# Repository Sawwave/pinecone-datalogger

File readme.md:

Arm based Datalogger running the Atmel SAM D20 MCU.

The Pinecone logger is a specialized, yet inexpensive data logger intended for sensing environmental variables. The ease of use and low cost of these datalogger systems make them ideal for mass deployment over a large area, allowing measurement of spatially-distributed data, rather than just a time-series of one point from a single logger.

The logger supports the following sensors natively:
	DHT-22 Temperature and Humidity sensor
	1 potentiometer implemented as a point dendrometer with 14 bits of precision
	multiple ports supporting sensors implementing the SDI-12 interface, which includes most Decagon brand sensors
	1 sap flow sensor implemented with a heating element and 4 thermocouples.

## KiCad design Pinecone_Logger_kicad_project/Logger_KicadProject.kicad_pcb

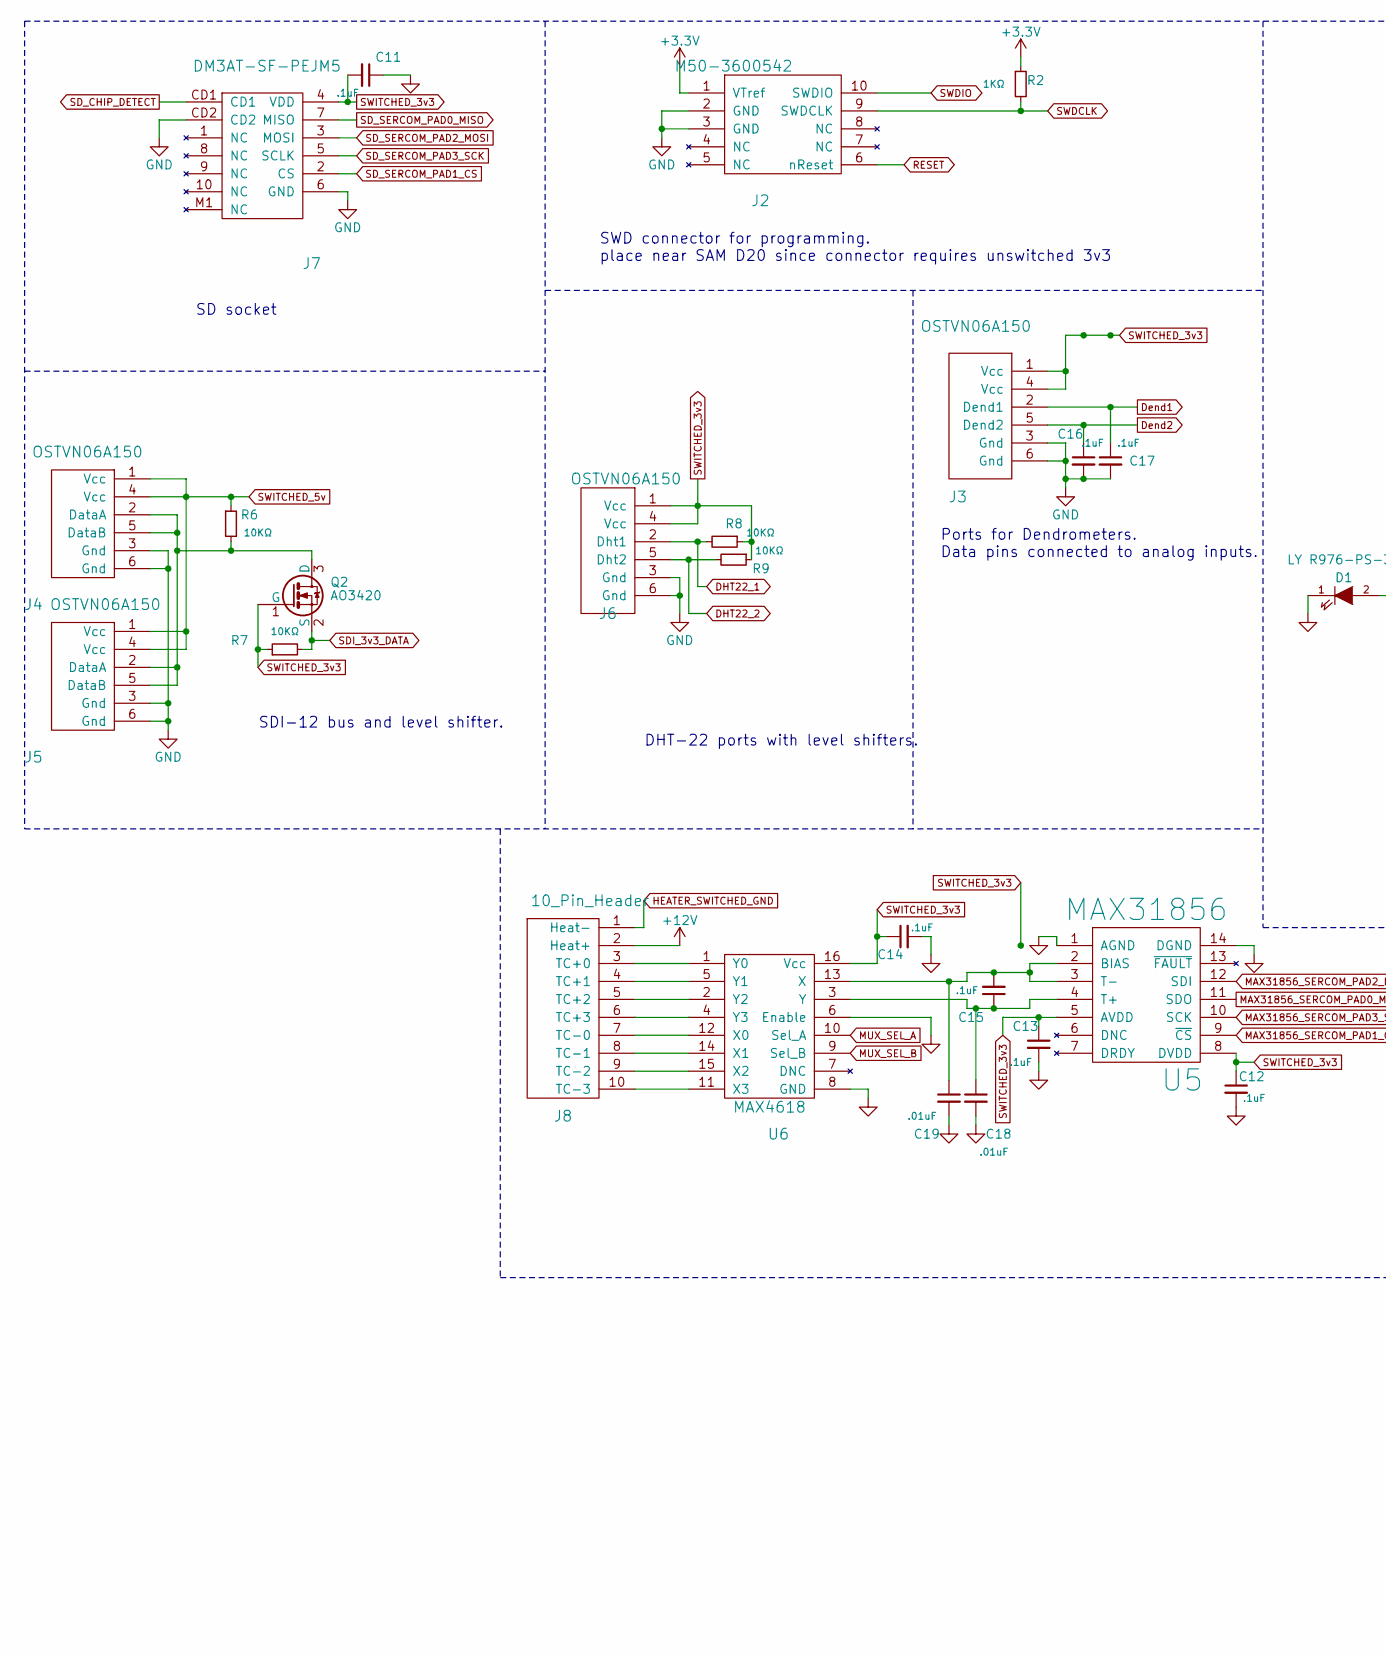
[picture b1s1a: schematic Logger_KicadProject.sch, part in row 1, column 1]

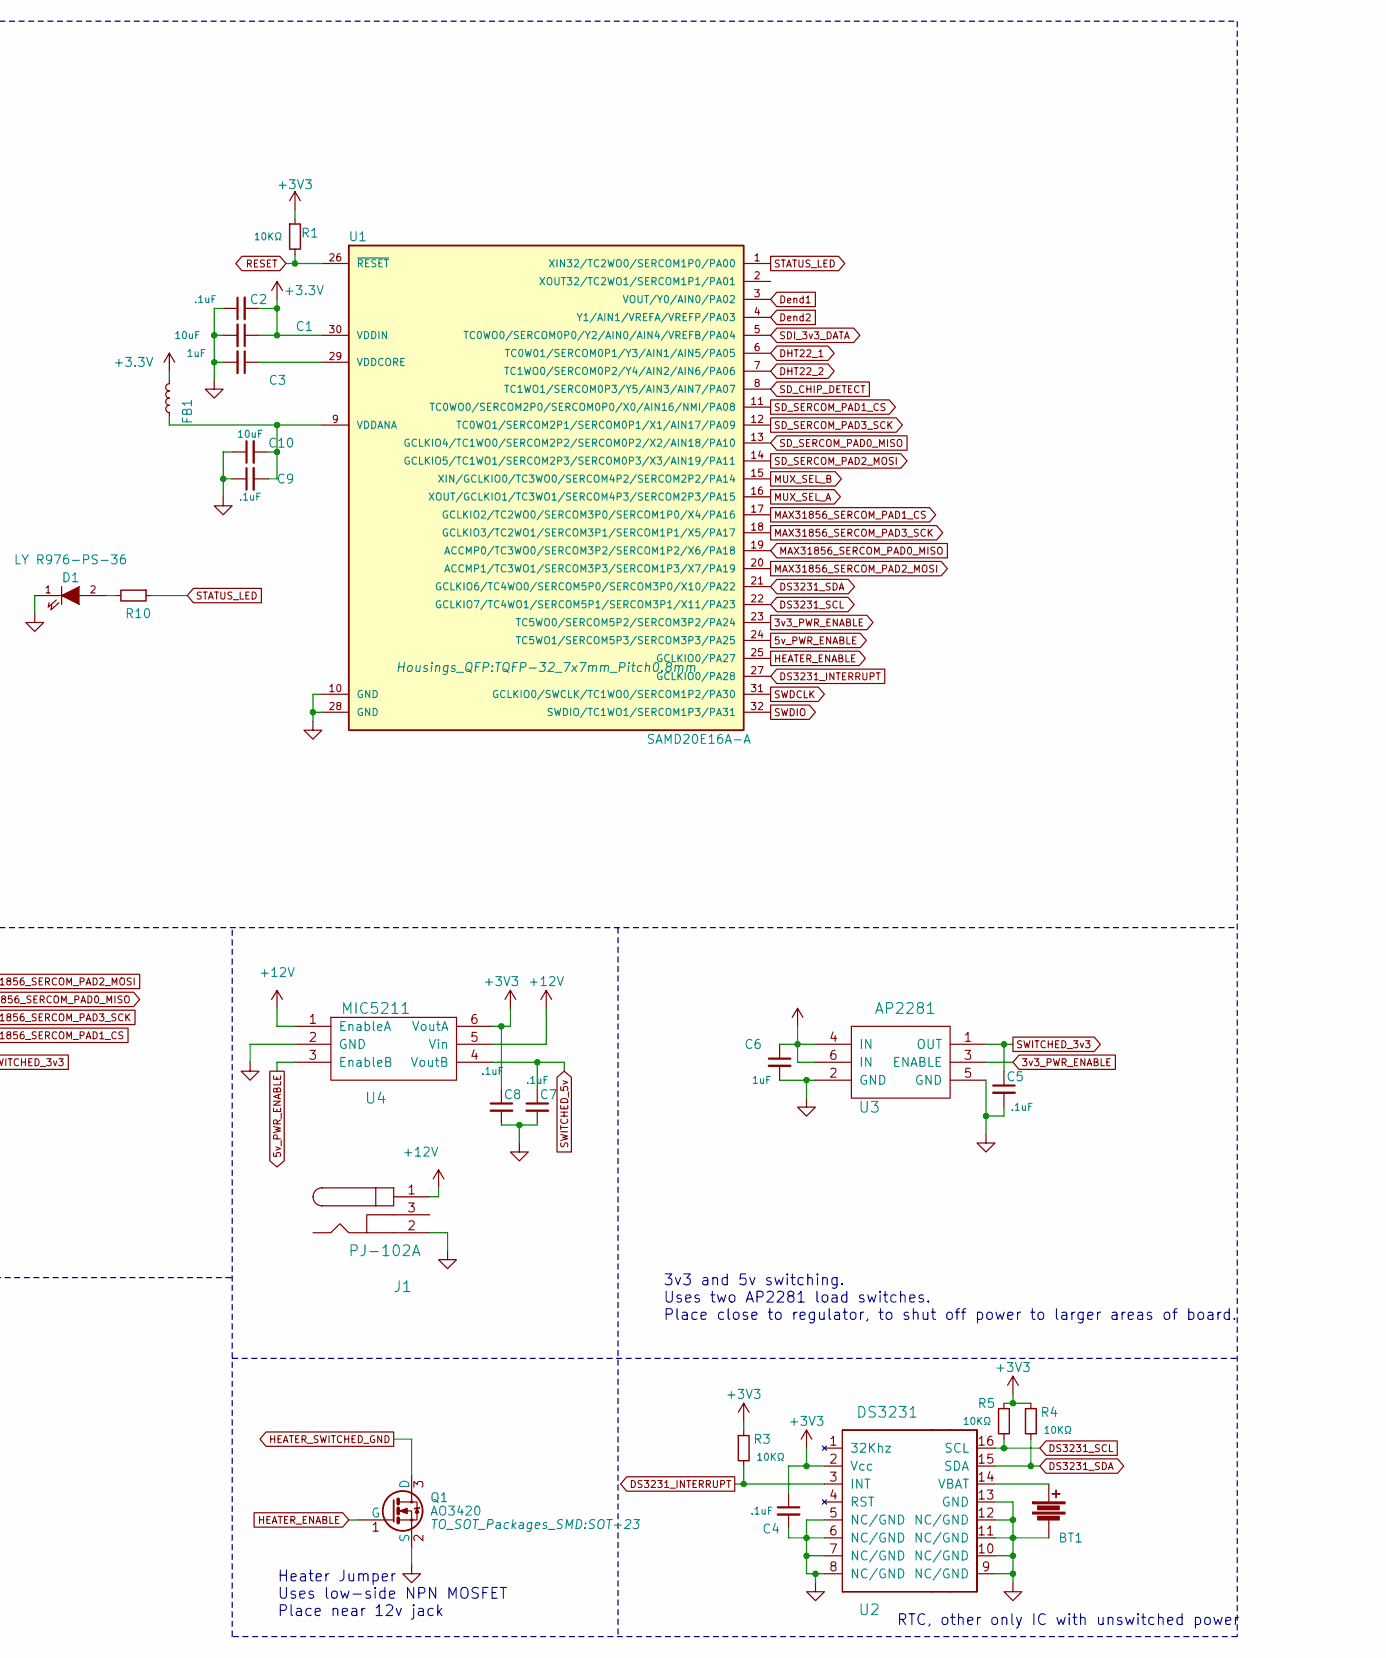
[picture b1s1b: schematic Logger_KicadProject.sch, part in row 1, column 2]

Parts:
BT1: Battery; S8201R_Batt_Holder; Part Id S8201-46R
C1, C10: GRM219R61A106KE44D; C_0805
C2, C4, C5, C7, C8, C9, C11, C12, C13, C14, C15, C16, C17: C0805C104K5RACTU; C_0805
C3, C6: GRM21BR71C105KA01L; C_0805
C18, C19: C0805C103K5RACTU; C_0805
D1: LY R976-PS-36; LED_0805
FB1: Z0805C221APMST; R_0805
J1: PJ-102A
J2: M50-3600542; 10_Pin_Cortex_SMD
J3, J4, J5, J6: OSTVN06A150; OSTVN06A150_6_Pin_Terminal
J7: DM3AT-SF-PEJM5; Hirose_DM3AT
J8: 10_Pin_Header; OSTVN10A150_10_pin_term
Q1, Q2: AO3420; SOT-23
R1, R3, R4, R5, R6, R7, R8, R9: RC0805JR-0710KL; R_0805
R2: RC0805JR-071KL; R_0805
R10: RC0805JR-0768RL; R_0805
U1: SAMD20E16A-A; TQFP-32_7x7mm_Pitch0.8mm
U2: DS3231; SOIC-16W_7.5x10.3mm_Pitch1.27mm
U3: AP2281; SOT-23-6
U4: MIC5211; SOT-23-6
U5: MAX31856; TSSOP-14
U6: MAX4618; SO-16-N

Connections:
3v3_PWR_ENABLE: U1.23 (TC5WO0/SERCOM5P2/SERCOM3P2/PA24), U3.3 (ENABLE)
5v_PWR_ENABLE: U1.24 (TC5WO1/SERCOM5P3/SERCOM3P3/PA25), U4.3 (EnableB)
+12V: J1.1, J8.2 (Heat+), U4.1 (EnableA), U4.5 (Vin)
DHT22_1: J6.2 (Dht1), R8.2, U1.6 (TC0W01/SERCOM0P1/Y3/AIN1/AIN5/PA05)
DHT22_2: J6.5 (Dht2), R9.2, U1.7 (TC1WO0/SERCOM0P2/Y4/AIN2/AIN6/PA06)
DS3231_INTERRUPT: R3.2, U1.27 (GCLKIO0/PA28), U2.3 (INT)
DS3231_SCL: R5.2, U1.22 (GCLKIO7/TC4WO1/SERCOM5P1/SERCOM3P1/X11/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), U2.16 (SCL)
DS3231_SDA: R4.2, U1.21 (GCLKIO6/TC4WO0/SERCOM5P0/SERCOM3P0/X10/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), U2.15 (SDA)
Dend1: C17.1, J3.2 (Dend1), U1.3 (VOUT/Y0/AIN0/PA02)
Dend2: C16.1, J3.5 (Dend2), U1.4 (Y1/AIN1/VREFA/VREFP/PA03)
GND: BT1.2, C1.2, C2.1, C3.2, C4.2, C5.2, C6.2, C7.2, C8.2, C9.1, C10.1, C11.1, C12.2, C13.2, C14.2, C16.2, C17.2, C18.2, C19.2, D1.1 (K), J1.2, J2.2 (GND), J2.3 (GND), J3.3 (Gnd), J3.6 (Gnd), J4.3 (Gnd), J4.6 (Gnd), J5.3 (Gnd), J5.6 (Gnd), J6.3 (Gnd), J6.6 (Gnd), J7.6 (GND), J7.CD2, Q1.2 (S), U1.10 (GND), U1.28 (GND), U2.5 (NC/GND), U2.6 (NC/GND), U2.7 (NC/GND), U2.8 (NC/GND), U2.9 (NC/GND), U2.10 (NC/GND), U2.11 (NC/GND), U2.12 (NC/GND), U2.13 (GND), U3.2 (GND), U3.5 (GND), U4.2 (GND), U5.1 (AGND), U5.14 (DGND), U6.6 (Enable), U6.8 (GND)
HEATER_ENABLE: Q1.1 (G), U1.25 (GCLKIO0/PA27)
HEATER_SWITCHED_GND: J8.1 (Heat-), Q1.3 (D)
MAX31856_SERCOM_PAD0_MISO: U1.19 (ACCMP0/TC3WO0/SERCOM3P2/SERCOM1P2/X6/PA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), U5.11 (SDO)
MAX31856_SERCOM_PAD1_CS: U1.17 (GCLKIO2/TC2WO0/SERCOM3P0/SERCOM1P0/X4/P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), U5.9 (~CS)
MAX31856_SERCOM_PAD2_MOSI: U1.20 (ACCMP1/TC3WO1/SERCOM3P3/SERCOM1P3/X7/PA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), U5.12 (SDI)
MAX31856_SERCOM_PAD3_SCK: U1.18 (GCLKIO3/TC2WO1/SERCOM3P1/SERCOM1P1/X5/P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), U5.10 (SCK)
MUX_SEL_A: U1.16 (XOUT/GCLKIO1/TC3WO1/SERCOM4P3/SERCOM2P3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), U6.10 (Sel_A)
MUX_SEL_B: U1.15 (XIN/GCLKIO0/TC3WO0/SERCOM4P2/SERCOM2P2/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), U6.9 (Sel_B)
unnamed: BT1.1, U2.14 (VBAT)
unnamed: C3.1, U1.29 (VDDCORE)
unnamed: C9.2, C10.2, FB1.1, U1.9 (VDDANA)
unnamed: C15.1, C18.1, U5.4 (T+), U6.3 (Y)
unnamed: C15.2, C19.1, U5.2 (BIAS), U5.3 (T-), U6.13 (X)
unnamed: D1.2 (A), R10.2
unnamed: J4.2 (DataA), J4.5 (DataB), J5.2 (DataA), J5.5 (DataB), Q2.3 (D), R6.2
unnamed: J8.3 (TC+0), U6.1 (Y0)
unnamed: J8.4 (TC+1), U6.5 (Y1)
unnamed: J8.5 (TC+2), U6.2 (Y2)
unnamed: J8.6 (TC+3), U6.4 (Y3)
unnamed: J8.7 (TC-0), U6.12 (X0)
unnamed: J8.8 (TC-1), U6.14 (X1)
unnamed: J8.9 (TC-2), U6.15 (X2)
unnamed: J8.10 (TC-3), U6.11 (X3)
RESET: J2.6 (nReset), R1.2, U1.26 (~RESET~)
SDI_3v3_DATA: Q2.2 (S), R7.2, U1.5 (TC0WO0/SERCOM0P0/Y2/AIN0/AIN4/VREFB/PA04)
SD_CHIP_DETECT: J7.CD1, U1.8 (TC1WO1/SERCOM0P3/Y5/AIN3/AIN7/PA07)
SD_SERCOM_PAD0_MISO: J7.7 (MISO), U1.13 (GCLKIO4/TC1WO0/SERCOM2P2/SERCOM0P2/X2/A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)
SD_SERCOM_PAD1_CS: J7.2 (CS), U1.11 (TC0WO0/SERCOM2P0/SERCOM0P0/X0/AIN16/NMI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)
SD_SERCOM_PAD2_MOSI: J7.3 (MOSI), U1.14 (GCLKIO5/TC1WO1/SERCOM2P3/SERCOM0P3/X3/A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)
SD_SERCOM_PAD3_SCK: J7.5 (SCLK), U1.12 (TC0WO1/SERCOM2P1/SERCOM0P1/X1/AIN17/PA09)
STATUS_LED: R10.1, U1.1 (XIN32/TC2WO0/SERCOM1P0/PA00)
SWDCLK: J2.9 (SWDCLK), R2.2, U1.31 (GCLKIO0/SWCLK/TC1WO0/SERCOM1P2/PA30)
SWDIO: J2.10 (SWDIO), U1.32 (SWDIO/TC1WO1/SERCOM1P3/PA31)
SWITCHED_3v3: C5.1, C11.2, C12.1, C13.1, C14.1, J3.1 (Vcc), J3.4 (Vcc), J6.1 (Vcc), J6.4 (Vcc), J7.4 (VDD), Q2.1 (G), R7.1, R8.1, R9.1, U3.1 (OUT), U5.5 (AVDD), U5.8 (DVDD), U6.16 (Vcc)
SWITCHED_5v: C7.1, J4.1 (Vcc), J4.4 (Vcc), J5.1 (Vcc), J5.4 (Vcc), R6.1, U4.4 (VoutB)

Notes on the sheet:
3v3 and 5v switching. Uses two AP2281 load switches. Place close to regulator, to shut off power to larger areas of board.
SDI-12 bus and level shifter.
Heater Jumper Uses low-side NPN MOSFET Place near 12v jack
DHT-22 ports with level shifters.
SWD connector for programming. place near SAM D20 since connector requires unswitched 3v3
Ports for Dendrometers. Data pins connected to analog inputs.
RTC, other only IC with unswitched power
SD socket

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
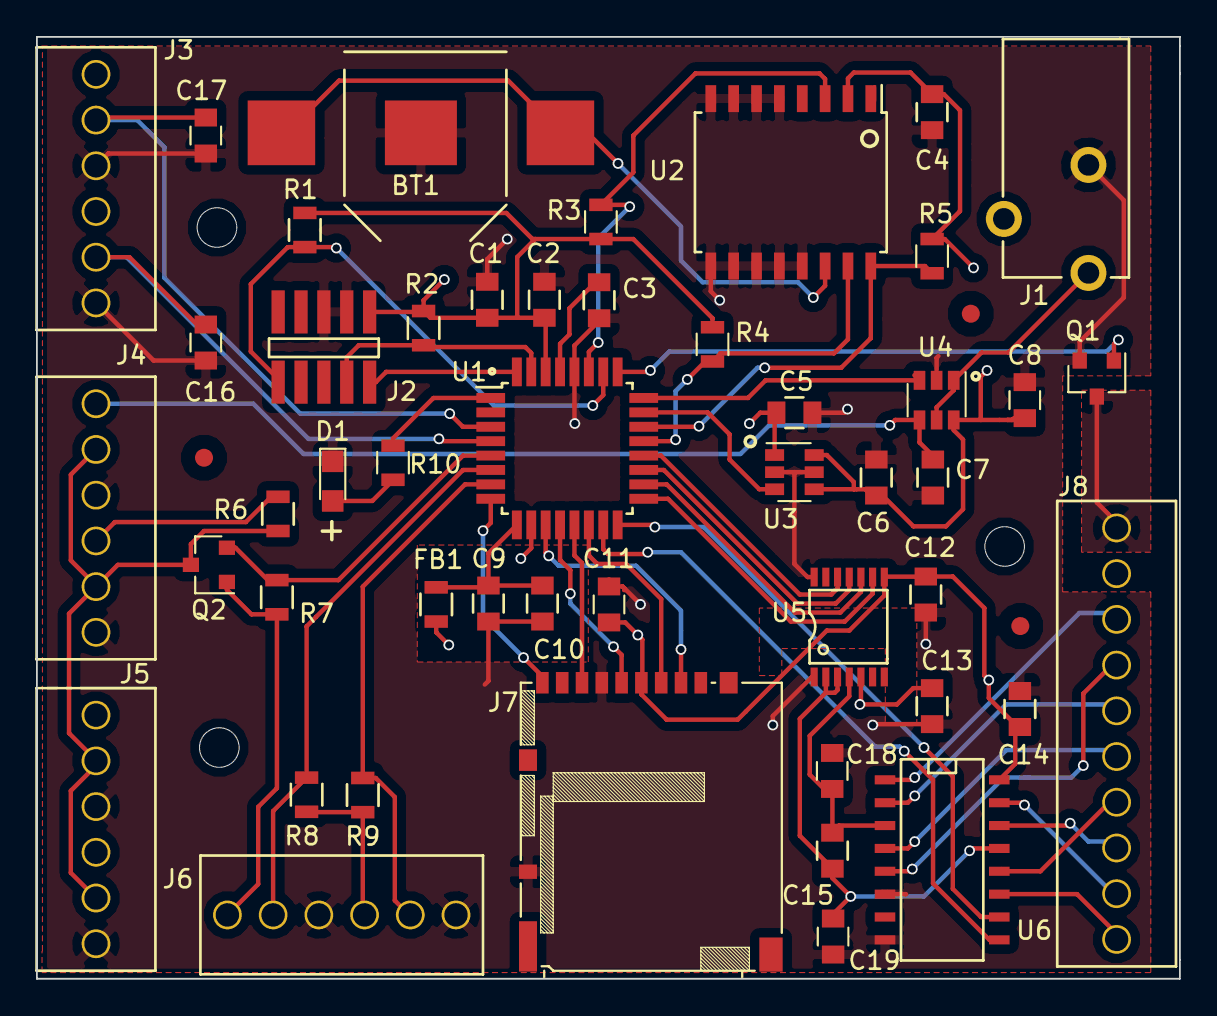
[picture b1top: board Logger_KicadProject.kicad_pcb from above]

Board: 4 copper layers, 63.5 x 52.3 mm, 51 parts (0 on the bottom side), 47 nets.

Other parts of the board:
FID1, FID2, FID3: Fiducial_1mm_Dia_2.54mm_Outer_CopperTop

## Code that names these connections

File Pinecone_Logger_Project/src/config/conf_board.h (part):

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//#define BIT_TIMING_DELAY_CYCLES						955		//833us bit timing


// avoid PA30 and PA31, these are for SWCLK and SWDIO respectively
//Put all IN and OUT data GPIOs on the lower 16 pins to make WRCONFIG access easier.
//pins that are only OUT can be on the top 16

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
#ifdef USING_SAMD20XPLAINED

#define DHT22_1_PINMASK								1 << 8							// PIN_PA08
#define DHT22_2_PINMASK								1 << 9							// PIN_PA09
#define DHT22_ALL_PINMASK							DHT22_1_PINMASK | DHT22_2_PINMASK

#define SDI_PIN										PIN_PA10
#define SDI_PIN_PINMASK								1 << 10

#define DEND_ANALOG_PIN_1							ADC_POSITIVE_INPUT_PIN0			//PIN_PA02
#define DEND_PORT_PIN_1								PIN_PA02
#define DEND_ANALOG_PIN_2							ADC_POSITIVE_INPUT_PIN1			//PIN_PA03
#define DEND_PORT_PIN_2								PIN_PA03

#define DS1302_DATA_PIN_INDEX						11
#define DS1302_CLOCK_PIN_INDEX						12
#define DS1302_ENABLE_PIN_INDEX						28
#define DS1302_DATA_PINMASK							1 << DS1302_DATA_PIN_INDEX		//PIN_PA11
#define DS1302_CLOCK_PINMASK						1 << DS1302_CLOCK_PIN_INDEX		//PIN_PA12
#define DS1302_ENABLE_PINMASK						1 << DS1302_ENABLE_PIN_INDEX	//PIN_PA28
#define DS1302_ALL_PINMASK							 DS1302_DATA_PINMASK | DS1302_CLOCK_PINMASK | DS1302_ENABLE_PINMASK


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#define MAX31856_SPI_PAD1							PINMUX_PA17C_SERCOM1_PAD1	//unused
#define MAX31856_SPI_PAD2							PINMUX_PA18C_SERCOM1_PAD2	//mosi
#define MAX31856_SPI_PAD3							PINMUX_PA19C_SERCOM1_PAD3	//sck
#define MAX31856_CS_PIN								PIN_PA17

#define SD_SERCOM_MODULE							SERCOM0
#define SD_PINMUX_SETTING							SPI_SIGNAL_MUX_SETTING_K	//chip detect on unused PA08, SCK, MISO, MOSI, and CD on PA0
#define SD_SPI_PIN0									PINMUX_PA04D_SERCOM0_PAD0	//chip detect
#define SD_SPI_PIN1									PINMUX_PA05D_SERCOM0_PAD1	//SCK
#define SD_SPI_PIN2									PINMUX_PA06D_SERCOM0_PAD2	//MISO
#define SD_SPI_PIN3									PINMUX_PA07D_SERCOM0_PAD3	//MOSI
#define SD_CS_PIN									PIN_PA14
#define SD_PIN_DETECT_LEVEL							0
#define SD_PIN_DETECT								PIN_PA11
#define SD_PIN_DETECT								PIN_PA11

//Mosfet PINS
#define SDI_DHT22_POWER_MOSFET_PINMASK				1 << 27	//PIN_PA24
#define HEATER_MOSFET_PINMASK						1 << 27	//PIN_PA25
#define DENDRO_TC_AMP_MOSFET_PINMASK				1 << 27	//PIN_PA27
#define SD_CARD_MOSFET_PINMASK						1 << 27	//PIN_PA28			
#define ALL_MOSFET_PINMASK							SDI_DHT22_POWER_MOSFET_PINMASK | HEATER_MOSFET_PINMASK | DENDRO_TC_AMP_MOSFET_PINMASK | SD_CARD_MOSFET_PINMASK

//TC Mux select
#define TC_MUX_SELECT_A_PINMASK						1 << 27 //PIN_PA22
#define TC_MUX_SELECT_B_PINMASK						1 << 27 //PIN_PA23
#define TC_MUX_SELECT_ALL_PINMASK					TC_MUX_SELECT_A_PINMASK | TC_MUX_SELECT_B_PINMASK


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
#ifdef FIRST_PRINT_PINSET

#define DHT22_1_PINMASK								1 << 6							// PIN_PA07
#define DHT22_2_PINMASK								1 << 7							// PIN_PA08
#define DHT22_ALL_PINMASK							DHT22_1_PINMASK | DHT22_2_PINMASK

#define SDI_PIN										PIN_PA00
#define SDI_PIN_PINMASK								1 << 0

#define DEND_ANALOG_PIN_1							ADC_POSITIVE_INPUT_PIN4			//PIN_PA04
#define DEND_ANALOG_PIN_2							ADC_POSITIVE_INPUT_PIN5			//PIN_PA05
#define DENDROMETER_TRAVEL_DISTANCE_MICROMETERS		12700.0	//12.7 millimeters

#define MAX31856_THERMOCOUPLE_TYPE_USED				MAX31856_THERMOCOUPLE_TYPE_T
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#define DS1302_DATA_PIN_INDEX						2
#define DS1302_CLOCK_PIN_INDEX						1
#define DS1302_ENABLE_PIN_INDEX						3
#define DS1302_DATA_PINMASK							1 << DS1302_DATA_PIN_INDEX		//PIN_PA02
#define DS1302_CLOCK_PINMASK						1 << DS1302_CLOCK_PIN_INDEX		//PIN_PA01
#define DS1302_ENABLE_PINMASK						1 << DS1302_ENABLE_PIN_INDEX	//PIN_PA03
#define DS1302_ALL_PINMASK							 DS1302_DATA_PINMASK | DS1302_CLOCK_PINMASK | DS1302_ENABLE_PINMASK


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#define MAX31856_SPI_PAD1							PINMUX_PA17C_SERCOM1_PAD1	//sck
#define MAX31856_SPI_PAD2							PINMUX_PA18C_SERCOM1_PAD2	//miso
#define MAX31856_SPI_PAD3							PINMUX_PA19C_SERCOM1_PAD3	//mosi
#define MAX31856_CS_PIN								PIN_PA16

#define SD_SERCOM_MODULE							SERCOM0
#define SD_PINMUX_SETTING							SPI_SIGNAL_MUX_SETTING_K
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#define SD_SPI_PIN1									PINMUX_PA09C_SERCOM0_PAD1	//SCK
#define SD_SPI_PIN2									PINMUX_PA10C_SERCOM0_PAD2	//MISO
#define SD_SPI_PIN3									PINMUX_PA11C_SERCOM0_PAD3	//MOSI
#define SD_CS_PIN									PIN_PA14
#define SD_PIN_DETECT								PIN_PA08
#define SD_PIN_DETECT_LEVEL							LOW

//Mosfet PINS
#define PWR_3V3_POWER_ENABLE						1 << 25
#define PWR_5V_POWER_ENABLE							1 << 27
#define ALL_POWER_ENABLE							PWR_3V3_POWER_ENABLE | PWR_5V_POWER_ENABLE
#define HEATER_MOSFET_PINMASK						1 << 28 //PIN_PA28

//TC Mux select
#define TC_MUX_SELECT_A_PINMASK						1 << 23 //PIN_PA22
#define TC_MUX_SELECT_B_PINMASK						1 << 22 //PIN_PA23
#define TC_MUX_SELECT_ALL_PINMASK					TC_MUX_SELECT_A_PINMASK | TC_MUX_SELECT_B_PINMASK

#define ALL_GPIO_PINMASK							ALL_POWER_ENABLE | HEATER_MOSFET_PINMASK | DS1302_ALL_PINMASK | DHT22_ALL_PINMASK | TC_MUX_SELECT_ALL_PINMASK | SDI_PIN_PINMASK
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#define DS3231_EXTINT_MUX							MUX_PA28A_EIC_EXTINT8
#define DS3231_EIC_LINE								8

#define DHT22_1_PINMASK								1 << 5							// PIN_PA06
#define DHT22_2_PINMASK								1 << 6							// PIN_PA07
#define DHT22_ALL_PINMASK							DHT22_1_PINMASK | DHT22_2_PINMASK

#define SDI_PIN										PIN_PA04
#define SDI_PIN_PINMASK								1 << 4

#define DEND_ANALOG_PIN_1							ADC_POSITIVE_INPUT_PIN0			//PIN_PA02
#define DEND_ANALOG_PIN_2							ADC_POSITIVE_INPUT_PIN1			//PIN_PA03
#define DENDROMETER_TRAVEL_DISTANCE_MICROMETERS		12700.0	//12.7 millimeters

#define MAX31856_THERMOCOUPLE_TYPE_USED				MAX31856_THERMOCOUPLE_TYPE_T
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#define MAX31856_SPI_PAD1							PINMUX_PA17C_SERCOM1_PAD1	//sck
#define MAX31856_SPI_PAD2							PINMUX_PA18C_SERCOM1_PAD2	//miso
#define MAX31856_SPI_PAD3							PINMUX_PA19C_SERCOM1_PAD3	//mosi
#define MAX31856_CS_PIN								PIN_PA16

#define SD_SERCOM_MODULE							SERCOM0
#define SD_PINMUX_SETTING							SPI_SIGNAL_MUX_SETTING_K
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#define SD_SPI_PIN1									PINMUX_PA09C_SERCOM0_PAD1	//SCK
#define SD_SPI_PIN2									PINMUX_PA10C_SERCOM0_PAD2	//MISO
#define SD_SPI_PIN3									PINMUX_PA11C_SERCOM0_PAD3	//MOSI
#define SD_CS_PIN									PIN_PA08
#define SD_PIN_DETECT								PIN_PA07
#define SD_PIN_DETECT_LEVEL							LOW

#define LED_PIN										0
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#define PWR_3V3_POWER_ENABLE						1 << 24
#define PWR_5V_POWER_ENABLE							1 << 25
#define ALL_POWER_ENABLE							PWR_3V3_POWER_ENABLE | PWR_5V_POWER_ENABLE
#define HEATER_MOSFET_PINMASK						1 << 27 //PIN_PA27

//TC Mux select
#define TC_MUX_SELECT_A_PINMASK						1 << 14 //PIN_PA14
#define TC_MUX_SELECT_B_PINMASK						1 << 15 //PIN_PA51
#define TC_MUX_SELECT_ALL_PINMASK					TC_MUX_SELECT_A_PINMASK | TC_MUX_SELECT_B_PINMASK

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
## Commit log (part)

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2016-10-18 initial commit, setup completed.
2016-10-18 Added readme
2016-10-18 moved readme
2016-10-18 added in SDI12 functionality
2016-10-18 Added in Dendro code
2016-10-18 Moved dendro travel distance to a board config macro
2016-10-18 Added DHT22 code, needs to be reworked to be in line with more robust SDI-12 code
2016-10-19 fixed typo in dht comment
2016-10-19 added TimedSleep, and the TimerCounter module
2016-10-19 added existing macros, fixed missing return in Max31856CheckWritterRegister
2016-10-19 added DS1302, will clean it up and optimize later
2016-10-21 changed data format to json
2016-10-21 added function to create new file if missing, and have it be an empty json array
2016-10-21 fixed bugs with new implementations
2016-10-24 added files that really should've been added. I hope
2016-10-24 changed datafile back to csv after a good talk with Patrick
2016-10-24 started on SDI12 metadata recording
2016-10-24 refactored the previous parsing into own function
2016-10-24 more config file stuff
2016-10-25 finished createDataFileIfMissing, now queries sensors and creates headers appropriately
2016-10-25 more sd card stuff
2016-10-27 copied over code sections from WORKING SD/MMC example project, hopefully works
2016-10-27 Got SD card stuff working! now to do more testing with config files and seeking with the data file.
2016-10-28 unit testing config file read/writing
2016-10-28 added testing for time file, will complete and run on Monday
2016-10-31 unit tested dateTimeFile read/writing
2016-10-31 added in MOSFET pin macros, created functionality to repair last line of data file. NEEDS TESTING
2016-11-01 changed ds1302 setDateTime to pass datetime pointer
2016-11-01 fixed bugs in file integrity check, added timedSleep initialization and startup code
2016-11-01 moved pins around and changed macros to better facilitate SAM D20E with no PORTB, only 32 PORTA pins
2016-11-01 moved checkValidity function for datafile higher in file to be with other, non unit test functions
2016-11-01 changed function argument lists to consolidate data that's not needed outside file util functions
2016-11-02 working on dendro code
2016-11-02 removed adc begin and end from dendro, inforced const-ness
2016-11-02 consolidated thermocouple reading into single function for all 4 TCs, including the mux selection
2016-11-02 added start conversion to dendro reading
2016-11-02 more work on ports and pinmask defines
2016-11-02 added in main functionality to query sdi sensors.
2016-11-03 changed DS1302 to use PORTA instead of ASF GPIO fiddling, rearranged pin definitions in confboard to support SAM D20E
2016-11-03 SDI12 now uses PORTA instead of asf port_pin stuff
2016-11-03 configured TimedSleep clocks
2016-11-03 now sleeps at end of loop
2016-11-03 main now logs all values to the SD card, and sets/clears the write in progress bit in the DS1302 register
2016-11-03 data values from all but datetime and SDI-12 now stored contiguously to facilitate easy file writing
2016-11-04 checking file integrity now doesn't return anything
2016-11-04 added more documentation to max31856
2016-11-04 refactored out Ds1302 init
2016-11-04 refactored out SDI-12 init
2016-11-04 removed reference to unfinished log file filename
2016-11-04 refactored dateTimeBuffer formatting into main, so it doesn't get done every loop
2016-11-04 refactored all sap flux system logging code to it's own function
2016-11-04 refactored SD initial bootstrapping into own function
2016-11-04 SdCardInit now no loger returns a value
2016-11-07 removed componentInit, and transferred SAM D20 hardware setup to beginning of main
2016-11-07 moved SDI metadata bootstrapping out of file utils and into main init function
2016-11-07 removed checkFileIntegrity flag, just uses DS1302 register now.
2016-11-07 max31856 now enables and disables SPI hardware when needed.
2016-11-07 refactored SDI-12 logging and datafile writing to own functions
2016-11-21 fixing stack overflow that's causing hard faults
2016-11-21 I AM A STUPID SANDWICH f_mount takes ptr to FATFS that must stay in scope. FATFA doesn't get copied
2016-11-23 now code fully supports passing FATFS and not being stupid
2016-11-23 changed writing values to use f_write instead of snprints
2016-11-23 moved newline into datetime buffer to automatically add a new line with each measurement.
2016-11-23 extracted sdiColumnHeaderSize to own variable in creating data file header.
2016-11-23 added max attempts to Max31856 spi unlocking
2016-11-23 added spi max tries to MAX31856 reading, too
2016-11-23 more spi max tries in reading!
2016-11-28 refactored sdi metadata function name
2016-11-28 changed datetime parsing to be mm/dd/yy
2016-11-28 refactored sdi Metadata gathering to own function
2016-11-28 readConfigFile now void, since it never returned false, anyway
2016-11-29 max31856 get temp now sets the out variable to NAN if in error state
2016-11-29 removed SDI metadata command, since it's not supported by all sensors
2016-11-29 removed sdigetMetadata from main
2016-11-29 started transition to config-stored num sdi values
2016-11-29 DHT22 now uses floats instead of doubles for consistency
2016-11-30 moved writing to sd and querying SDI into main loop
2016-11-30 logging time, vals, and SDI now have own methods
2016-12-02 configured dendro ADC module to use 1/2*Vcc reference and 1/2 input gain
2016-12-02 finishing touches on dendro that make it more accurate
2016-12-02 consolidated MOSFET off messages to be clearer
2016-12-02 enforced PascalCase for all functions
2016-12-02 reorganized and recommented code for TimedSleep
2016-12-02 changed name of SDI_12.c to SDI12.c to better conform with rest of project
2016-12-02 reorganized and consolidated comments for SDI12
2016-12-02 reorganized MAX31856, and added block comments
2016-12-02 consolidated block comments in dendro
2016-12-05 changed DHT22 time threshold, and value casting to float
2016-12-05 fixed tracking files?
2016-12-05 fixed bug with multiple D_! commands for SDI12
2016-12-06 got sdi12 working again, refactored name for SDI12_ParseNumValuesFromResponse
2016-12-07 fixed spi locking for MAX31856
2016-12-07 enabled Max31856 open-circuit detection
2016-12-07 consolidated dendro calculations into one macro multiplication
2016-12-08 dendro ADC working correctly now. Was causing errors when adc was only temporarily enabled
2016-12-12 added brown out detection
2016-12-12 reordered init functions, now can initial sleep before writing the header.
2016-12-13 put some refining touches on BOD detection.
2016-12-13 ifdef'd out SDI12 unit tests
2016-12-13 reorganized includes, no major changes
2016-12-13 added defaults to loggerConfig, set in ReadConfigFile
2016-12-14 implemented sd writing of float values using gcvtf
2016-12-14 fixed bug in SDI12 headers, now should create headers correctly.
2016-12-14 fixed bug in parsing the SDI sensor number of values for more than 1 sensor.
2016-12-14 SDI headers are no 1 indexed, rather than 0 indexed.
2016-12-14 fixed arg order for an f_puts command, changed num digits precision float to string to 9
2016-12-14 fixed time.txt parsing
2016-12-14 added kicad project
2016-12-29 finished schematic design, created netlist
2017-01-04 pcb partially done, pushing to work remotely
2017-01-20 finished circuit design, firmware needs updating to respect pin changes
2017-01-20 created extended gerbers
2017-01-24 touched up footprint
2017-01-30 bunch of minor changes, changed DS1302 crystal to through hole with correst ESD
2017-02-15 completed revision of circuit design, remapped pins in conf_board
2017-02-15 added brownout detection loop at beginning of startup
2017-02-23 added looping check for sd card
2017-02-24 changed SOT-23 MOSFETS to have correct pinout. design should work with AO3420's now
2017-02-24 changed schematic to use DS3231
2017-02-27 added MAX3231 to board, changed xlator mosfets to work
2017-03-03 Finished Logger V2 design, ready for pcb order
2017-03-09 logger circuit design finished, and ordered
2017-03-13 implemented library for DS3231
2017-03-13 updated schematic and pcb to correctly use SAM D20 E18, not the E16
2017-03-15 implemented DS3231
2017-03-16 implemented external interrupt sleep mode with DS3231 interrupt
2017-03-16 changed config file parsing to use newly made config flags
2017-03-16 refactored sap flux enable flag
2017-03-16 implemented dendrometer disable configuration
2017-03-16 implemented DHT-22 disable configuration
2017-03-16 refactored the dht22 system out into own function
2017-03-16 implemented SDI-12 disable configuration
2017-03-21 added code for LED codes
2017-03-21 changed sd mount/init to have maximum attempts, and return success or failure
2017-03-21 changed sd init to repeat failure LED signal on fail
2017-03-21 reincluded creating header file if missing
2017-03-21 added LedCodes folder
2017-03-21 implemented success status code before main loop
2017-03-21 included LedCodes in main because I am a derpus
2017-03-22 removed old testing filedws
2017-03-22 added BOM to repo
2017-03-22 LedCodes now sets LED to output for flashing, and back to input after for power saving
2017-03-22 configured DHT IO pins to lower power mode when not in use
2017-03-22 TimedSleep now sets all gpio to power saving
2017-03-22 removed DS1302 defines from conf_board, set ds1302 code to ignore compilation
2017-03-22 set all pins to low power mode before sleeping each loop
2017-03-22 set MAX4618 select pins to low power when not in use
2017-03-22 12v power mosfet now set to low power when not in use
2017-03-22 rewrote the trashpile that was the stock SD card initialization
2017-03-23 fixed unknown issues with SD card reading
2017-03-23 fixed bug where ds3231 registers were parsing digits in wrong order
2017-03-23 now flashes on startup and on each logging start
2017-03-23 fixed time setting to include year, too
2017-03-23 fixed MAX31856 CS pin macro
2017-03-23 finally fixed MAX31856, oh god
2017-03-25 added timer counter for timing SDI12 interface
2017-03-25 implemented SDI12 interface using timer counters, testing needed
2017-03-27 removed interrupt disabling on sdi-12 to allow for timer counter timings
2017-03-28 fixed SDI-12 timings for release
2017-03-29 removed sdi-12 timer counters.
2017-03-30 DS3231 alarm working properly
2017-03-30 finished implementing alarm from time buffer and logging interval
2017-04-20 SD card no longer wastes power through SERCOM bus
2017-04-20 reverted to older SDI-12 code, now functions correctly
2017-04-20 added multiple attempt loop to RTC I2C connections
2017-04-20 implemented correct retries and timing for SDI-12
2017-04-20 added more attempts to I2C transactions for DS3231
2017-04-20 added delay in SDI-12 response searching to allow for multiple sensors
2017-04-20 refactored i2c send/recieve for DS3231
2017-04-20 moved DS3231 packet direction enum to c file, since it's not needed externally
2017-04-20 starting on hour now has a backup alarm of 61 minutes
2017-04-20 refactored out function enabling extint wakeup, putting it in both sleep functions by default
2017-04-20 made main.c a little cleaner
2017-04-20 brownout detection now correctly enables on startup
2017-04-20 BOD on startup now wakes up for 1us to give detection time to check, just in case
2017-04-21 removed old testing functions from fileutils
2017-04-21 renamed function to create data file with header
2017-04-21 renamed function for reading time file
2017-04-21 reordered/renamed functions in FileUtils
2017-06-21 reorganized schematic, getting ready for publication
2017-07-10 changed heater pulse duration to 3 seconds to reflect Burgess et al
2017-08-15 Create LICENSE
2017-08-24 Moved gerber files to a more prominent directory
2017-08-24 moved bill of materials to top level

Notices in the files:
Pinecone_Logger_Project/src/config/conf_board.h:
Copyright (C) 2012-2015 Atmel Corporation. All rights reserved.
